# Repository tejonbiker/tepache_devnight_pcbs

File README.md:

# tepache_devnight_pcbs
En este repositorio encontrarán la presentación de la plática en Dev Night Tepache Hacklab.

La plática consta de una pequeña demostración de como hacer una PCB, la plática es meramente introductoria, 
la idea es servir de introducción y demostración que hacer PCBs es algo que cualquiera puede hacer con un poco
de dedicación.

Además se muestran los datos de algunos negocios que pueden proveer estas tarjetas (algunos en Guanajuato).

Federico Ramos

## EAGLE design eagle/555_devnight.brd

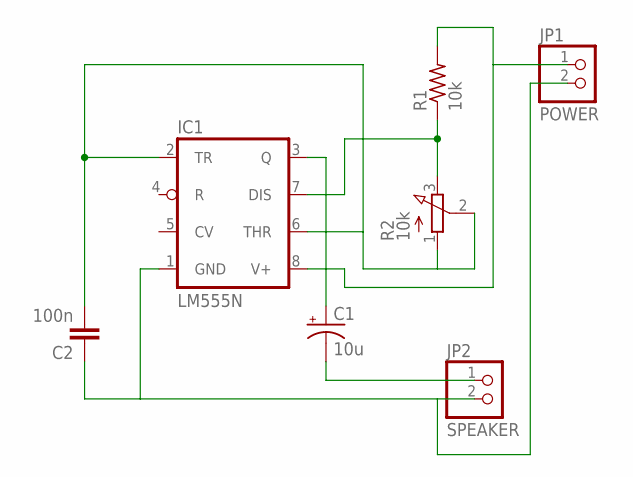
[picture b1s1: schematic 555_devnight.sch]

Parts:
C1: 10u; E3,5-8
C2: 100n; C050-025X075
IC1: LM555N; DIL08-ROUND
JP1: POWER; 1X02
JP2: SPEAKER; 1X02
R1: 10k; 0207/10
R2: 10k; 3RP/1610N

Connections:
unnamed: IC1.8 (V+), JP1.1, R1.2
unnamed: IC1.7 (DIS), R1.1, R2.3 (E)
unnamed: C1.+, IC1.3 (Q)
unnamed: C1.-, JP2.1
unnamed: C2.1, IC1.1 (GND), JP1.2, JP2.2
unnamed: C2.2, IC1.2 (TR), IC1.6 (THR), R2.1 (A), R2.2 (S)

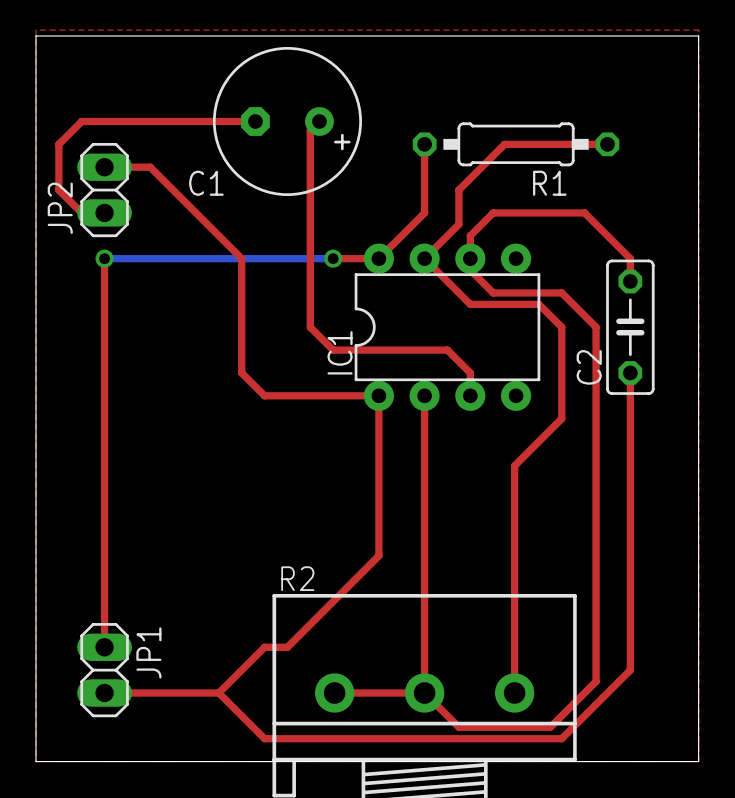
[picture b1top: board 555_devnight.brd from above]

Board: 2 copper layers, 36.8 x 40.3 mm, 7 parts (0 on the bottom side), 6 nets.

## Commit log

2017-07-29 primer commit realizado, se agrega la presentacion en pdf y los archivos eagle de la platica
2017-08-26 bitshake fue agregado a la parte de servicios de PCBs
